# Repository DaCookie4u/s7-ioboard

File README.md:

# s7-ioboard
Input simulation board for Siemens S7 PLCs

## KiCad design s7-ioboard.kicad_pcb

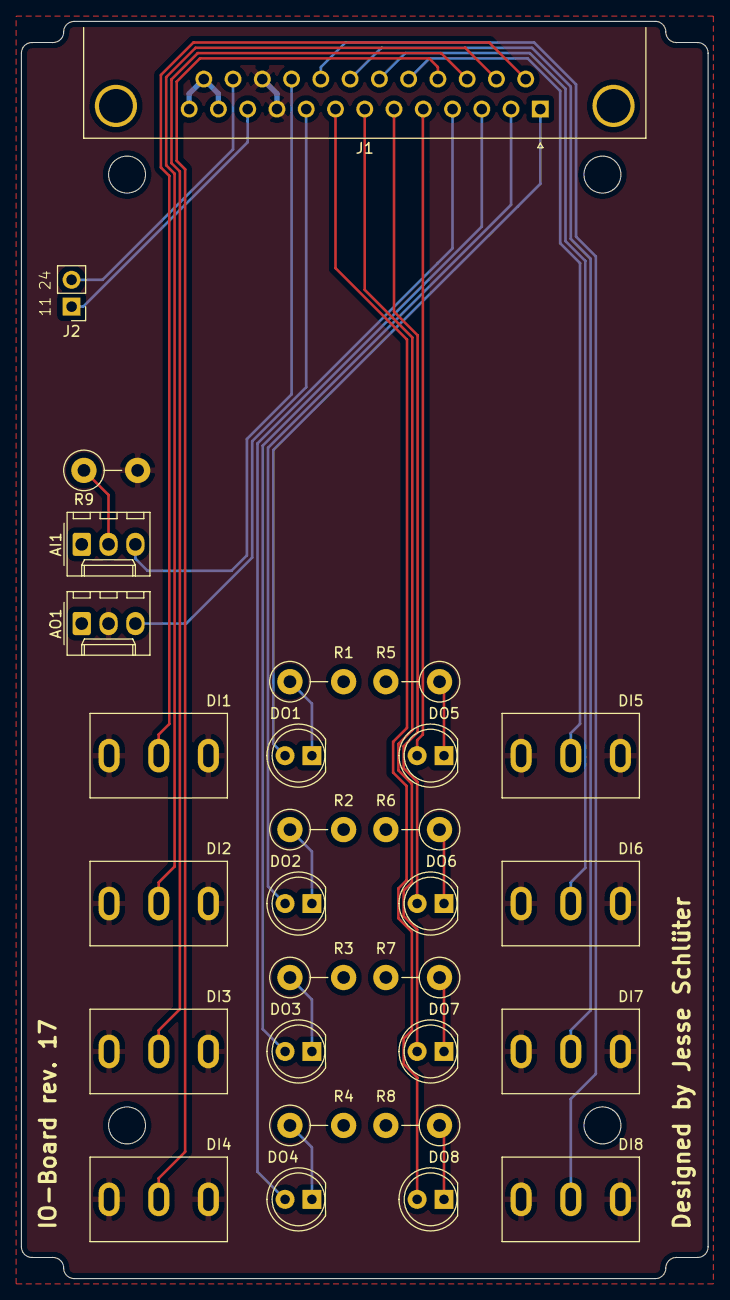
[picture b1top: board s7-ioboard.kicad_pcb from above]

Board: 2 copper layers, 65.0 x 119.0 mm, 29 parts (0 on the bottom side), 31 nets.

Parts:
AI1: Conn_01x03_Male; Molex_KK-254_AE-6410-03A_1x03_P2.54mm_Vertical
AO1: Conn_01x03_Male; Molex_KK-254_AE-6410-03A_1x03_P2.54mm_Vertical
DI1, DI2, DI3, DI4, DI5, DI6, DI7, DI8: SW_SPDT; MTS-113
DO1, DO2, DO3, DO4, DO5, DO6, DO7, DO8: LED; LED_D5.0mm
J1: DB25_Male; DSUB-25_Male_Horizontal_P2.77x2.84mm_EdgePinOffset4.94mm_Ho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
J2: Conn_01x02_Male; PinHeader_1x02_P2.54mm_Vertical
R1, R2, R3, R4, R5, R6, R7, R8, R9: R; R_Axial_DIN0411_L9.9mm_D3.6mm_P5.08mm_Vertical

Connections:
/AW: AO1.3, J1.9
/An.1: DO1.2, J1.1
/An.2: DO2.2, J1.2
/An.3: DO3.2, J1.3
/An.4: DO4.2, J1.4
/An.5: DO5.2, J1.5
/An.6: DO6.2, J1.6
/An.7: DO7.2, J1.7
/An.8: DO8.2, J1.8
/EW: AI1.3, J1.22
/En.1: DI1.2, J1.14
/En.2: DI2.2, J1.15
/En.3: DI3.2, J1.16
/En.4: DI4.2, J1.17
/En.5: DI5.2, J1.18
/En.6: DI6.2, J1.19
/En.7: DI7.2, J1.20
/En.8: DI8.2, J1.21
/L+Sensor: AO1.2, DI1.1, DI1.3, DI2.1, DI2.3, DI3.1, DI3.3, DI4.1, DI4.3, DI5.1, DI5.3, DI6.1, DI6.3, DI7.1, DI7.3, DI8.1, DI8.3, J1.10, J1.23, R9.2
/Masse: AI1.1, AO1.1, J1.12, J1.13, J1.25, R1.2, R2.2, R3.2, R4.2, R5.2, R6.2, R7.2, R8.2
unnamed: AI1.2, R9.1
unnamed: DO1.1, R1.1
unnamed: DO2.1, R2.1
unnamed: DO3.1, R3.1
unnamed: DO4.1, R4.1
unnamed: DO5.1, R5.1
unnamed: DO6.1, R6.1
unnamed: DO7.1, R7.1
unnamed: DO8.1, R8.1
unnamed: J1.11, J2.1
unnamed: J1.24, J2.2

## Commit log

2020-04-07 Added comments to scl functionblock
2020-04-12 Updated to revision 17
2020-04-12 Renamend to versionless file
